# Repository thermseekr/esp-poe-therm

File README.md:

# ESP-POE-THERM
 ESP32 based board for heated floor temperature control, equipped with a temperature and humidity sensor for ambient monitoring and a NTC sensor for floor temperature monitoring.

## VERSION HISTORY

ESP-POE-THERM-V1 - Initial release.

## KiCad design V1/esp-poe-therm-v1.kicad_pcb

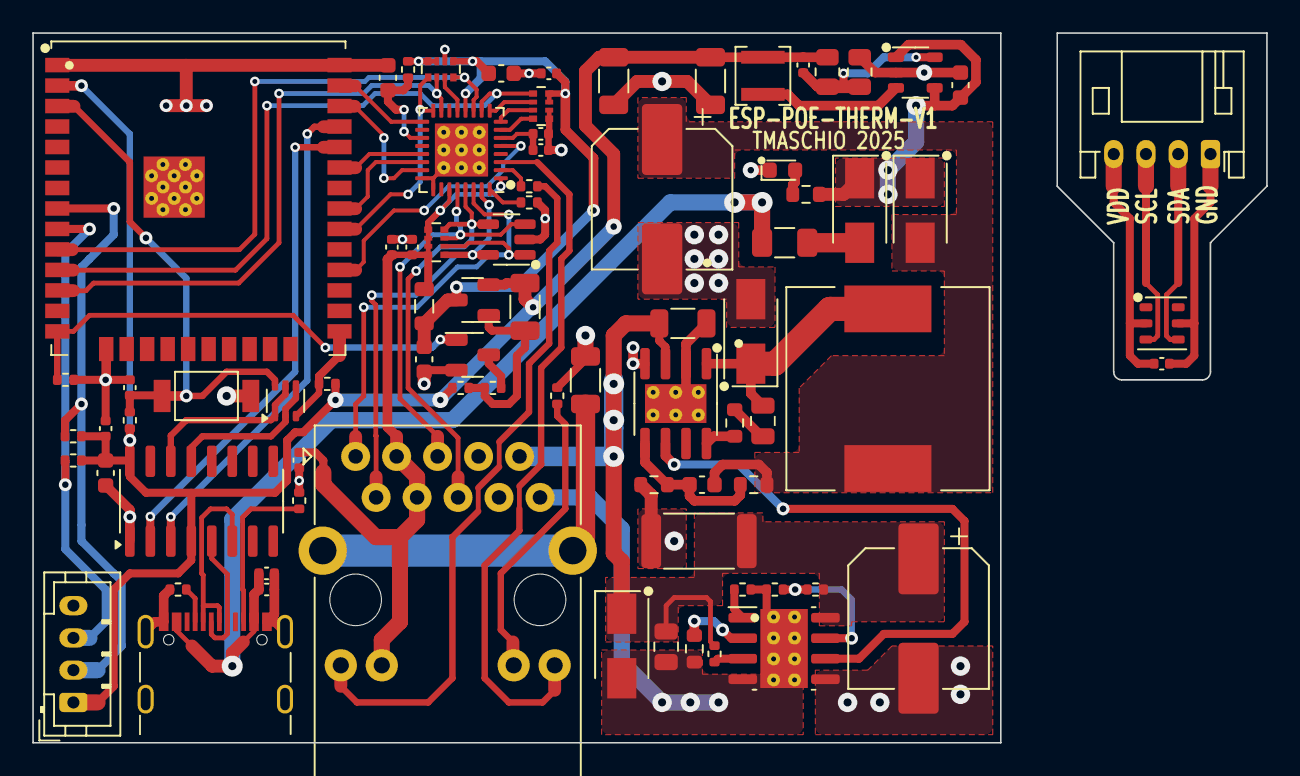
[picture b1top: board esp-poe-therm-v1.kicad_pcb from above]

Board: 2 copper layers, 76.5 x 44.0 mm, 80 parts (0 on the bottom side), 67 nets.

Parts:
C1, C3: 100nF/100V; C_0805_2012Metric
C2: 22uF/100V; CP_Elec_8x10.5
C4: 12pF/50V; C_0603_1608Metric
C5: 470uF/16V; CP_Elec_8x10.5
C6, C12, C15, C19, C25: 10uF/10V; C_0603_1608Metric
C7: 22pF/50V; C_0402_1005Metric
C8, C9, C24: 22uF/10V; C_1206_3216Metric
C10, C14, C20: 1uF/25V; C_0402_1005Metric
C11, C13, C16, C17, C18, C23, C26: 100nF/50V; C_0402_1005Metric
C21: 470pF/50V; C_0402_1005Metric
C22: 1nF/2kV; C_1206_3216Metric
D1: SMAJ58A; D_SMA
D2: SS510; D_SMA
D3, D4: SS34; D_SMA
D5: GREEN; LED_0603_1608Metric
D6: ESDS314DBV; SOT-23-5
F1: 500mA; Fuse_1206_3216Metric
J1: USB_C_Receptacle_USB2.0; USB_C_Receptacle_GCT_USB4105-xx-A_16P_TopMnt_Horizontal
J2: RJ45 JACK; RJ45_HanRun_HY931147C
J3: Sensor Temperatura; JST_PH_B4B-PH-K_1x04_P2.00mm_Vertical
J4: Sensor Temperatura; JST_PH_S4B-PH-K_1x04_P2.00mm_Horizontal
L1: 33uH/2,1A; L_12x12mm_h6mm
L2: 2,2uH/1,5A; L_3x3mm_h1.5mm
L3: 2A/600R; L_0805_2012Metric
Q1: UMH3N; SOT-363_SC-70-6
Q2: WPM2015-3/TR; SOT-23
Q3: LMUN2211LT1G; SOT-23
R1: 130k/62,5mW; R_0402_1005Metric
R2, R16, R17, R18, R19, R23: 10k/62,5mW; R_0402_1005Metric
R3: 180k/62,5mW; R_0402_1005Metric
R4: 4,42k/100mW; R_0603_1608Metric
R5: 30,1k/62,5mW; R_0402_1005Metric
R6: 4,7k/1W; R_2512_6332Metric
R7: 30mR/250mW; R_1206_3216Metric
R8: 5,1R/100mW; R_0603_1608Metric
R9: 300k/100mW; R_0603_1608Metric
R10: 52,3k/100mW; R_0603_1608Metric
R11: 820R/100mW; R_0603_1608Metric
R12: 100k/0,125W; R_0805_2012Metric
R13: 22,1k/0,125W; R_0805_2012Metric
R14, R15: 5,1k/62,5mW; R_0402_1005Metric
R20: 12,1k/62,5mW; R_0402_1005Metric
R21, R22: 330R/62,5mW; R_0402_1005Metric
R24: 1k/62,5mW; R_0402_1005Metric
R25, R26: 2k2/62,5mW; R_0402_1005Metric
RN1, RN2: 4x2,2k/62,5mW; R_Array_Convex_4x0402
RN3: 4x49,9R/62,5mW; R_Array_Convex_4x0402
SW1: RESET; SW_SPST_Xunpu_TS1088AR02016
U1: TPS2376DDAR-H; SOIC-8-1EP_3.9x4.9mm_P1.27mm_EP2.95x4.9mm_Mask2.71x3.4mm_Th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
U2: TX4138; SOIC-8-1EP_3.9x4.9mm_P1.27mm_EP2.41x3.81mm_ThermalVias
U3: SY8089A1AAC; SOT-23-5_Shorter_Pins
U4: CH340C; SOIC-16_3.9x9.9mm_P1.27mm
U5: ESP32-WROOM-32UE-N4; ESP32-WROOM-32U
U6: LAN8710A; QFN-32-1EP_5x5mm_P0.5mm_EP3.3x3.3mm_ThermalVias
U7: AHT20; DFN-6-3x3mm_P1mm

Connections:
5VPOE: C4.1, C5.1, D3.2 (A), L1.2, R9.1
5VUSB: D4.2 (A), F1.1
+3.3V: C7.1, C8.1, C9.1, C12.1, C13.1, C24.1, J3.1, L2.2, Q2.2 (S), R12.1, R16.1, R17.1, R23.1, R25.1, R26.1, U4.4 (V3), U4.16 (VCC), U5.2 (VDD)
+3.3VA: C16.1, C18.1, C23.1, J2.3 (CT), J2.4 (CT), J2.13 (RLED+), L3.2, RN3.5 (R4.2), RN3.6 (R3.2), RN3.7 (R2.2), RN3.8 (R1.2), U6.1 (VDD2A), U6.27 (VDD1A)
+3.3VLAN: C17.1, C19.1, C25.1, L3.1, Q2.3 (D), R19.2, RN1.5 (R4.2), RN1.7 (R2.2), RN1.8 (R1.2), RN2.7 (R2.2), RN2.8 (R1.2), U6.12 (VDDIO)
+5V: C6.1, D3.1 (K), D4.1 (K), R11.1, U3.1 (EN), U3.4 (IN)
/EMAC_CLK: U5.28 (IO17), U6.5 (XTAL1/CLKIN)
/EMAC_MDC: U5.37 (IO23), U6.17 (MDC)
/EMAC_MDIO: RN1.1 (R1.1), U5.30 (IO18), U6.16 (MDIO)
/EMAC_RX: RN1.2 (R2.1), U5.12 (IO27), U6.15 (COL/CRS_DV/~MODE2)
/EMAC_RXD0: RN1.4 (R4.1), U5.10 (IO25), U6.11 (RXD0/~MODE0)
/EMAC_RXD1: RN2.1 (R1.1), U5.11 (IO26), U6.10 (RXD1/~MODE1)
/EMAC_TXD0: U5.31 (IO19), U6.22 (TXD0)
/EMAC_TXD1: U5.36 (IO22), U6.23 (TXD1)
/EMAC_TXEN: U5.33 (IO21), U6.21 (TXEN)
/I2C_SCL: J3.2, R25.2, U5.8 (IO32)
/I2C_SDA: J3.3, R26.2, U5.9 (IO33)
/LED_G_K: R21.2, U6.2 (LED2/~INTSEL)
/LED_Y_A: J2.11 (LLED+), U6.3 (LED1/~REGOFF)
/RD+: D6.5 (I/04), J2.2 (RD+), RN3.1 (R1.1), U6.31 (RXP)
/RD-: D6.1 (I/01), J2.1 (RD-), RN3.2 (R2.1), U6.30 (RXN)
/TD+: D6.4 (I/03), J2.6 (TD+), RN3.4 (R4.1), U6.29 (TXP)
/TD-: D6.3 (I/02), J2.5 (TD-), RN3.3 (R3.1), U6.28 (TXN)
/USB_D+: J1.A6 (D+), J1.B6 (D+), U4.5 (UD+)
/USB_D-: J1.A7 (D-), J1.B7 (D-), U4.6 (UD-)
GND: C2.2, C5.2, C6.2, C8.2, C9.2, C10.2, C11.2, C12.2, C13.2, C14.2, C15.1, C16.2, C17.2, C18.2, C19.2, C20.2, C21.2, C22.2, C23.2, C25.2, D2.2 (A), D5.1 (K), D6.2 (GND), J1.A1 (GND), J1.A12 (GND), J1.B1 (GND), J1.B12 (GND), J1.S1 (SHIELD), J3.4, Q3.2 (E), R6.2, R10.2, R13.2, R14.2, R15.2, R18.1, R20.2, R22.2, RN1.6 (R3.2), RN2.5 (R4.2), RN2.6 (R3.2), SW1.1, U1.5 (RTN), U2.4 (GND), U3.2 (GND), U4.1 (GND), U5.1 (GND), U5.15 (GND), U5.38 (GND), U5.39 (GND), U6.24 (TXD2), U6.25 (TXD3), U6.33 (VSS)
unnamed: C3.1, R8.1
unnamed: C10.1, C11.1, F1.2, J1.A4 (VBUS), J1.A9 (VBUS), J1.B4 (VBUS), J1.B9 (VBUS)
unnamed: C3.2, D2.1 (K), L1.1, U2.1 (SW)
unnamed: D5.2 (A), R11.2
unnamed: J1.A5 (CC1), R14.1
unnamed: J1.B5 (CC2), R15.1
unnamed: J2.12 (LLED-), R22.1
unnamed: J2.14 (RLED-), R21.1
unnamed: C22.1, J2.15 (SHIELD)
unnamed: C26.2, J4.1, U7.5 (GND)
unnamed: J4.2, U7.4 (SDA)
unnamed: J4.3, U7.3 (SCL)
unnamed: C26.1, J4.4, U7.2 (VDD)
unnamed: Q1.2 (B1), Q1.4 (E2), U4.13 (~DTR)
unnamed: C14.1, Q1.6 (C1), R16.2, SW1.2, U5.3 (EN)
unnamed: Q1.1 (E1), Q1.5 (B2), U4.14 (~RTS)
unnamed: Q1.3 (C2), R17.2, U5.25 (IO0)
unnamed: C24.2, Q2.1 (G), R23.2, R24.1
unnamed: Q3.3 (C), R24.2
unnamed: R7.2, U2.2 (ILIM), U2.9 (ILIM)
unnamed: RN1.3 (R3.1), U6.13 (RXER/RXD4/~PHYAD0)
unnamed: RN2.2 (R2.1), U6.9 (RXD2/~RMIISEL)
unnamed: RN2.3 (R3.1), U6.8 (RXD3/~PHYAD2)
unnamed: RN2.4 (R4.1), U6.7 (RXCLK/~PHYAD1)
unnamed: R4.1, U1.2 (CLASS)
unnamed: R5.2, U1.3 (DET)
unnamed: R3.1, U1.1 (ILIM)
unnamed: R1.2, R2.1, U1.7 (UVLO)
unnamed: R8.2, U2.8 (BS)
unnamed: C4.2, R9.2, R10.1, U2.5 (FB)
unnamed: C7.2, R12.2, R13.1, U3.5 (FB)
unnamed: L2.1, U3.3 (LX)
unnamed: U4.3 (RXD), U5.35 (TXD0/IO1)
unnamed: U4.2 (TXD), U5.34 (RXD0/IO3)
unnamed: R20.1, U6.32 (RBIAS)
unnamed: C20.1, C21.1, U6.6 (VDDCR)
unnamed: C15.2, R19.1, U6.19 (~RST)
PG: U1.6 (PG), U2.6 (EN)
PHY_PWR: Q3.1 (B), R18.2, U5.14 (IO12)
PoE+: C1.1, C2.1, D1.1 (K), J2.9 (V+), R1.1, R5.1, R6.1, R7.1, U1.8 (VDD), U2.3 (VIN)
PoE-: C1.2, D1.2 (A), J2.10 (V-), R2.2, R3.2, R4.2, U1.4 (VSS), U1.9 (PPAD)

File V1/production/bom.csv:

Designator,Footprint,Quantity,Value,LCSC Part #
"C1, C3",0805,2,100nF/100V,C28233
"C10, C14, C20",0402,3,1uF/25V,C52923
"C11, C13, C16, C17, C18, C23, C27, C29",0402,8,100nF/50V,C307331
"C12, C15, C19, C25, C6",0603,5,10uF/10V,C19702
C2,CP_Elec_8x10.5,1,22uF/100V,C178570
C21,0402,1,470pF/50V,C1537
C22,1206,1,1nF/2kV,C3013812
"C24, C8, C9",1206,3,22uF/10V,C5672
C28,0402,1,10nF/50V,
C4,0603,1,12pF/50V,C38523
C5,CP_Elec_8x10.5,1,470uF/16V,C96179
C7,0402,1,22pF/50V,C1555
D1,D_SMA,1,SMAJ58A,C132936
D2,D_SMA,1,SS510,C65010
"D3, D4",D_SMA,2,SS34,C8678
D5,0603,1,GREEN,C72043
D6,SOT-23-5,1,ESDS314DBV,C1847859
F1,1206,1,500mA,C151133
J1,USB_C_Receptacle_GCT_USB4105-xx-A_16P_TopMnt_Horizontal,1,USB_C_Receptacle_USB2.0,C2765186
J2,RJ45_HanRun_HY931147C,1,RJ45 JACK,C91754
J3,TerminalBlock_Dibo_DB141R-2.54-2P_1x02_P2.54mm_Horizontal,1,PT1000 RTD,C2898754
L1,L_12x12mm_h6mm,1,"33uH/2,1A",C169386
L2,L_3x3mm_h1.5mm,1,"2,2uH/1,5A",C370424
L3,0805,1,2A/600R,C139168
Q1,SOT-363_SC-70-6,1,UMH3N,C62892
Q2,SOT-23,1,WPM2015-3/TR,C558305
Q3,SOT-23,1,LMUN2211LT1G,C150229
R1,0402,1,"130k/62,5mW",C93946
R10,0603,1,"52,3k/100mW",C185323
R11,0603,1,820R/100mW,C23253
R12,0805,1,"100k/0,125W",C149504
R13,0805,1,"22,1k/0,125W",C17552
"R14, R15",0402,2,"5,1k/62,5mW",C105872
"R16, R17, R18, R19, R2, R23",0402,6,"10k/62,5mW",C60490
R20,0402,1,"12,1k/62,5mW",C25852
"R21, R22",0402,2,"330R/62,5mW",C25104
R24,0402,1,"1k/62,5mW",C11702
R25,0402,1,"4,02k/62,5mW",C852810
R3,0402,1,"180k/62,5mW",C138046
R4,0603,1,"4,42k/100mW",C482858
R5,0402,1,"30,1k/62,5mW",C138009
R6,2512,1,"4,7k/1W",C878291
R7,1206,1,30mR/250mW,C473665
R8,0603,1,"5,1R/100mW",C25197
R9,0603,1,300k/100mW,C23024
"RN1, RN2",R_Array_Convex_4x0402,2,"4x2,2k/62,5mW",C728724
RN3,R_Array_Convex_4x0402,1,"4x49,9R/62,5mW",C136850
SW1,SW_SPST_TL3342,1,RESET,C318884
U1,SOIC-8-1EP_3.9x4.9mm_P1.27mm_EP2.95x4.9mm_Mask2.71x3.4mm_ThermalVias,1,TPS2376DDAR-H,C544899
U2,SOIC-8-1EP_3.9x4.9mm_P1.27mm_EP2.41x3.81mm_ThermalVias,1,TX4138,C329267
U3,SOT-23-5_Shorter_Pins,1,SY8089A1AAC,C479074
U4,SOIC-16_3.9x9.9mm_P1.27mm,1,CH340C,C84681
U5,ESP32-WROOM-32U,1,ESP32-WROOM-32UE-N4,C701344
U6,QFN-32-1EP_5x5mm_P0.5mm_EP3.3x3.3mm_ThermalVias,1,LAN8710A,C46185
U8,TQFN-20-1EP_5x5mm_P0.65mm_EP3.25x3.25mm_ThermalVias,1,MAX31865xTP,C118474

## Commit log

2024-12-15 A lot of stuff
2024-12-16 Lots of stuff
2024-12-16 Finishing touches
2024-12-20 Case
2024-12-20 Update fp-info-cache
2024-12-21 Replace ESP32 for externa antena version
2025-05-28 Replace sensor type
2025-05-28 Replacing external for onboard sensor
2025-05-29 Updating sensor type
2025-05-30 Layout updated
2025-06-03 Work in progress
2025-06-03 Reducing board size
